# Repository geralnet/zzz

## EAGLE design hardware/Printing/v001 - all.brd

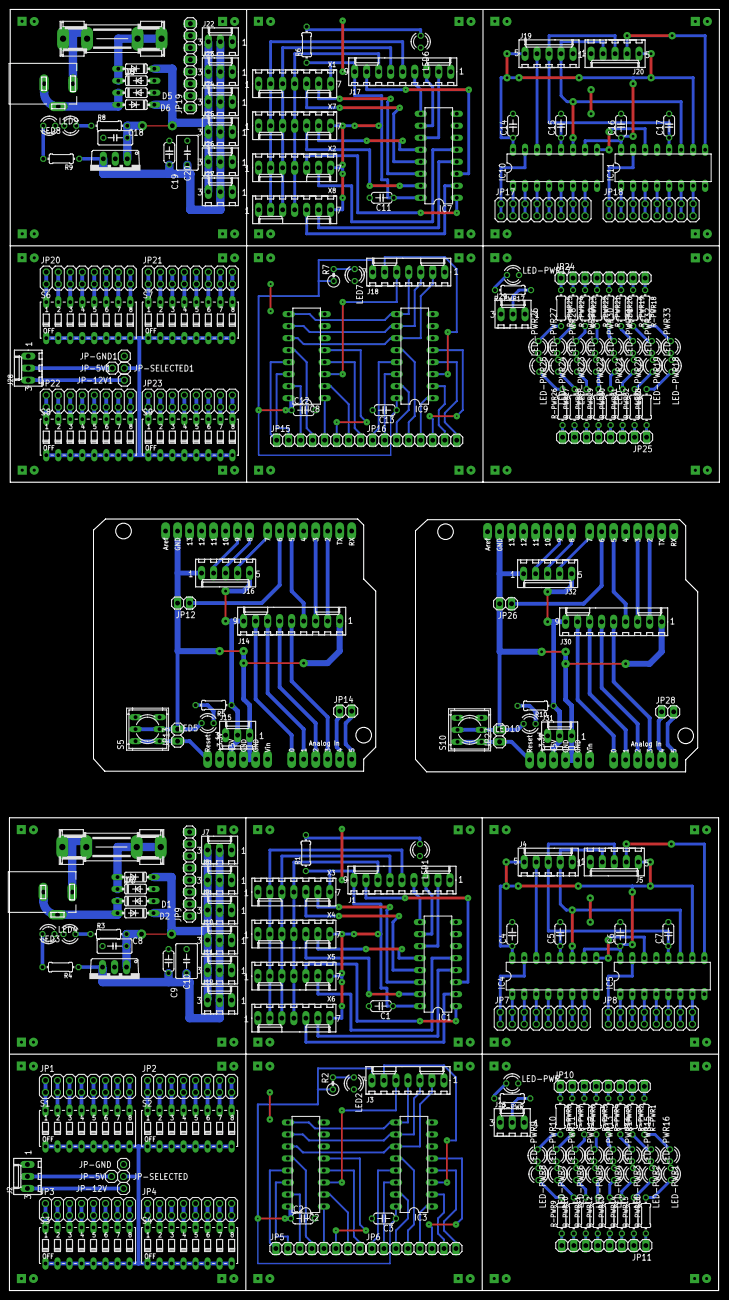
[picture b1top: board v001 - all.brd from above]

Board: 2 copper layers, 150.2 x 271.0 mm, 230 parts (0 on the bottom side), 322 nets.

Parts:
C1, C2, C3, C4, C5, C6, C7, C9, C11, C12, C13, C14, C15, C16, C17, C19: 0.1uF; C050-024X044
C8, C18: 0.33uF; C050-030X075
C10, C20: 1uF; C050-045X075
D1, D2, D3, D4, D5, D6, D7, D8: 1N4004; DO35-7
F1, F2: 3A; SHK20L
IC1, IC2, IC3, IC7, IC8, IC9: 4051N; DIL16
IC4, IC5, IC10, IC11: 74HC595N; DIL16
IC6, IC12: 7805TV; TO220V
J1, J17: To Arduino Shield; 6410-09
J2, J13, J15, J28, J29, J31: Power; 6410-03
J3, J18: Input; 6410-07
J4, J19: Input; 6410-05
J5, J20: Next Demux; 6410-05
J6, J21: 12VDC; DCJ0202
J7, J22: Out-1; 6410-03
J8, J23: Out-2; 6410-03
J9, J24: Out-3; 6410-03
J10, J25: Out-4; 6410-03
J11, J26: Out-5; 6410-03
J12, J27: Out-6; 6410-03
J14, J30: Primary Input Mux; 6410-09
J16, J32: Output Demux; 6410-05
JP1, JP2, JP3, JP4, JP20, JP21, JP22, JP23: 2X08
JP5, JP15: Input 1; 1X08
JP6, JP16: Input 2; 1X08
JP7, JP17: Output A; 2X08
JP8, JP18: Output B; 2X08
JP9, JP19: GND; 1X08
JP10, JP11, JP24, JP25: 1X08
JP12, JP14, JP26, JP28: Config; 1X02
JP13, JP27: Reset; 1X02
JP-5V, JP-5V1, JP-12V, JP-12V1: 1X01
JP-GND, JP-GND1: 1X01
JP-SELECTED, JP-SELECTED1: 1X01
LED1, LED2, LED5, LED6, LED7, LED10: Green; LED3MM
LED3, LED4, LED8, LED9: GREEN; LED3MM
LED-PWR, LED-PWR17: Green; LED3MM
LED-PWR1, LED-PWR2, LED-PWR3, LED-PWR4, LED-PWR5, LED-PWR6, LED-PWR7, LED-PWR8, LED-PWR9, LED-PWR10, LED-PWR11, LED-PWR12, LED-PWR13, LED-PWR14, LED-PWR15, LED-PWR16, LED-PWR18, LED-PWR19, LED-PWR20, LED-PWR21, LED-PWR22, LED-PWR23, LED-PWR24, LED-PWR25, LED-PWR26, LED-PWR27, LED-PWR28, LED-PWR29, LED-PWR30, LED-PWR31, LED-PWR32, LED-PWR33: Yellow; LED3MM
PCB1, PCB2, PCB3, PCB4, PCB5, PCB6, PCB7, PCB8, PCB9, PCB10, PCB11, PCB12: ZZZ_MODULE05X05; ZZZ_MODULE_05X05
R1, R3, R4, R5, R6, R8, R9, R10: 470R; 0204/7
R2, R7: 470R; 0207/2V
R-PWR, R-PWR1, R-PWR2, R-PWR3, R-PWR4, R-PWR5, R-PWR6, R-PWR7, R-PWR8, R-PWR9, R-PWR10, R-PWR11, R-PWR12, R-PWR13, R-PWR14, R-PWR15, R-PWR16, R-PWR17, R-PWR18, R-PWR19, R-PWR20, R-PWR21, R-PWR22, R-PWR23, R-PWR24, R-PWR25, R-PWR26, R-PWR27, R-PWR28, R-PWR29, R-PWR30, R-PWR31, R-PWR32, R-PWR33: 470R; 0204/7
S1, S2, S3, S4, S6, S7, S8, S9: DIP08S
S5, S10: 9077-2
U1, U2: ARDUINO_SHIELDLONGPADS; DUEMILANOVE_SHIELD_LONGPADS
X1, X3: Sec 12; 6410-07
X2, X5: Sec 56; 6410-07
X4, X7: Sec 34; 6410-07
X6, X8: Sec 78; 6410-07

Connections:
!CONFIGURATION: JP12.1, U1.D6
!CONFIGURATION1: JP26.1, U2.D6
!RESET: JP13.1, S5.1, S5.4, U1.RES
!RESET1: JP27.1, S10.1, S10.4, U2.RES
+5V: J2.2, JP-5V.1
+5V1: C1.1, IC1.16, J1.9, R1.1, X3.7, X4.7, X5.7, X6.7
+5V2: C2.1, C3.1, IC2.16, IC3.16, J3.7, R2.1
+5V3: C4.1, C6.1, IC4.10, IC4.16, IC5.10, IC5.16, J4.5, J5.5
+5V4: C9.1, C10.1, IC6.3, J7.2, J8.2, J9.2, J10.2, J11.2, J12.2, R4.1
+5V5: J13.2, R-PWR.1
+5V6: J14.9, J15.2, J16.5, R5.1, U1.5V
+5V7: C11.1, IC7.16, J17.9, R6.1, X1.7, X2.7, X7.7, X8.7
+5V8: C12.1, C13.1, IC8.16, IC9.16, J18.7, R7.1
+5V9: C14.1, C16.1, IC10.10, IC10.16, IC11.10, IC11.16, J19.5, J20.5
+5V10: C19.1, C20.1, IC12.3, J22.2, J23.2, J24.2, J25.2, J26.2, J27.2, R9.1
+5V11: J28.2, JP-5V1.1
+5V12: J29.2, R-PWR17.1
+5V13: J30.9, J31.2, J32.5, R10.1, U2.5V
+12V: J2.3, JP-12V.1
+12V1: C8.1, D2.C, D4.C, IC6.1, J7.3, J8.3, J9.3, J10.3, J11.3, J12.3, R3.2
+12V3: C18.1, D6.C, D8.C, IC12.1, J22.3, J23.3, J24.3, J25.3, J26.3, J27.3, R8.2
+12V4: J28.3, JP-12V1.1
GND: J2.1, JP-GND.1, PCB1.GND@1, PCB1.GND@2, PCB1.GND@3, PCB1.GND@4, PCB1.GND@5, PCB1.GND@6, PCB1.GND@7, PCB1.GND@8
GND1: C1.2, IC1.6, IC1.7, IC1.8, J1.1, LED1.K, PCB2.GND@1, PCB2.GND@2, PCB2.GND@3, PCB2.GND@4, PCB2.GND@5, PCB2.GND@6, PCB2.GND@7, PCB2.GND@8, X3.1, X4.1, X5.1, X6.1
GND2: C2.2, C3.2, IC2.6, IC2.7, IC2.8, IC3.6, IC3.7, IC3.8, J3.1, LED2.K, PCB3.GND@1, PCB3.GND@2, PCB3.GND@3, PCB3.GND@4, PCB3.GND@5, PCB3.GND@6, PCB3.GND@7, PCB3.GND@8
GND3: C4.2, C5.2, C6.2, C7.2, IC4.8, IC4.13, IC5.8, IC5.13, J4.1, J5.1, PCB4.GND@1, PCB4.GND@2, PCB4.GND@3, PCB4.GND@4, PCB4.GND@5, PCB4.GND@6, PCB4.GND@7, PCB4.GND@8
GND4: C8.2, C9.2, C10.2, D1.A, D3.A, IC6.2, J7.1, J8.1, J9.1, J10.1, J11.1, J12.1, JP9.1, JP9.2, JP9.3, JP9.4, JP9.5, JP9.6, JP9.7, JP9.8, LED3.K, LED4.K, PCB5.GND@1, PCB5.GND@2, PCB5.GND@3, PCB5.GND@4, PCB5.GND@5, PCB5.GND@6, PCB5.GND@7, PCB5.GND@8
GND5: J13.1, LED-PWR.K, LED-PWR1.K, LED-PWR2.K, LED-PWR3.K, LED-PWR4.K, LED-PWR5.K, LED-PWR6.K, LED-PWR7.K, LED-PWR8.K, LED-PWR9.K, LED-PWR10.K, LED-PWR11.K, LED-PWR12.K, LED-PWR13.K, LED-PWR14.K, LED-PWR15.K, LED-PWR16.K, PCB6.GND@1, PCB6.GND@2, PCB6.GND@3, PCB6.GND@4, PCB6.GND@5, PCB6.GND@6, PCB6.GND@7, PCB6.GND@8
GND6: J14.1, J15.1, J16.1, JP12.2, JP13.2, LED5.K, S5.2, S5.5, U1.GND@0, U1.GND@1, U1.GND@2
GND7: C11.2, IC7.6, IC7.7, IC7.8, J17.1, LED6.K, PCB7.GND@1, PCB7.GND@2, PCB7.GND@3, PCB7.GND@4, PCB7.GND@5, PCB7.GND@6, PCB7.GND@7, PCB7.GND@8, X1.1, X2.1, X7.1, X8.1
GND8: C12.2, C13.2, IC8.6, IC8.7, IC8.8, IC9.6, IC9.7, IC9.8, J18.1, LED7.K, PCB8.GND@1, PCB8.GND@2, PCB8.GND@3, PCB8.GND@4, PCB8.GND@5, PCB8.GND@6, PCB8.GND@7, PCB8.GND@8
GND9: C14.2, C15.2, C16.2, C17.2, IC10.8, IC10.13, IC11.8, IC11.13, J19.1, J20.1, PCB9.GND@1, PCB9.GND@2, PCB9.GND@3, PCB9.GND@4, PCB9.GND@5, PCB9.GND@6, PCB9.GND@7, PCB9.GND@8
GND10: C18.2, C19.2, C20.2, D5.A, D7.A, IC12.2, J22.1, J23.1, J24.1, J25.1, J26.1, J27.1, JP19.1, JP19.2, JP19.3, JP19.4, JP19.5, JP19.6, JP19.7, JP19.8, LED8.K, LED9.K, PCB10.GND@1, PCB10.GND@2, PCB10.GND@3, PCB10.GND@4, PCB10.GND@5, PCB10.GND@6, PCB10.GND@7, PCB10.GND@8
GND11: J28.1, JP-GND1.1, PCB11.GND@1, PCB11.GND@2, PCB11.GND@3, PCB11.GND@4, PCB11.GND@5, PCB11.GND@6, PCB11.GND@7, PCB11.GND@8
GND12: J29.1, LED-PWR17.K, LED-PWR18.K, LED-PWR19.K, LED-PWR20.K, LED-PWR21.K, LED-PWR22.K, LED-PWR23.K, LED-PWR24.K, LED-PWR25.K, LED-PWR26.K, LED-PWR27.K, LED-PWR28.K, LED-PWR29.K, LED-PWR30.K, LED-PWR31.K, LED-PWR32.K, LED-PWR33.K, PCB12.GND@1, PCB12.GND@2, PCB12.GND@3, PCB12.GND@4, PCB12.GND@5, PCB12.GND@6, PCB12.GND@7, PCB12.GND@8
GND13: J30.1, J31.1, J32.1, JP26.2, JP27.2, LED10.K, S10.2, S10.5, U2.GND@0, U2.GND@1, U2.GND@2
INPUT_1: IC2.13, JP5.1
INPUT_2: IC2.14, JP5.2
INPUT_3: IC2.15, JP5.3
INPUT_4: IC2.12, JP5.4
INPUT_5: IC2.1, JP5.5
INPUT_6: IC2.5, JP5.6
INPUT_7: IC2.2, JP5.7
INPUT_8: IC2.4, JP5.8
INPUT_9: IC3.13, JP6.1
INPUT_10: IC3.14, JP6.2
INPUT_11: IC3.15, JP6.3
INPUT_12: IC3.12, JP6.4
INPUT_13: IC3.1, JP6.5
INPUT_14: IC3.5, JP6.6
INPUT_15: IC3.2, JP6.7
INPUT_16: IC8.13, JP15.1
INPUT_17: IC8.14, JP15.2
INPUT_18: IC8.15, JP15.3
INPUT_19: IC8.12, JP15.4
INPUT_20: IC8.1, JP15.5
INPUT_21: IC8.5, JP15.6
INPUT_22: IC8.2, JP15.7
INPUT_23: IC8.4, JP15.8
INPUT_24: IC9.13, JP16.1
INPUT_25: IC9.14, JP16.2
INPUT_26: IC9.15, JP16.3
INPUT_27: IC9.12, JP16.4
INPUT_28: IC9.1, JP16.5
INPUT_29: IC9.5, JP16.6
INPUT_30: IC9.2, JP16.7
INPUT_READ: IC1.3, J1.8
INPUT_READ1: J14.8, U1.A0
INPUT_READ2: IC7.3, J17.8
INPUT_READ3: J30.8, U2.A0
IN_CLOCK: IC4.11, IC5.11, J4.2, J5.2
IN_CLOCK1: IC10.11, IC11.11, J19.2, J20.2
IN_DATA: IC4.14, J4.4
IN_DATA1: IC10.14, J19.4
IN_LATCH: C5.1, C7.1, IC4.12, IC5.12, J4.3, J5.3
IN_LATCH1: C15.1, C17.1, IC10.12, IC11.12, J19.3, J20.3
IN_SELECT_A: J14.2, U1.D2
IN_SELECT_A1: J30.2, U2.D2
IN_SELECT_B: J14.3, U1.D3
IN_SELECT_B1: J30.3, U2.D3
IN_SELECT_C: J14.4, U1.D5
IN_SELECT_C1: J30.4, U2.D5
IN_SELECT_D: J14.5, U1.A3
IN_SELECT_D1: J30.5, U2.A3
IN_SELECT_E: J14.6, U1.A2
IN_SELECT_E1: J30.6, U2.A2
IN_SELECT_F: J14.7, U1.A1
IN_SELECT_F1: J30.7, U2.A1
unnamed: JP3.1, JP3.2, S3.16
unnamed: JP3.3, JP3.4, S3.15
unnamed: LED1.A, R1.2
unnamed: JP1.1, JP1.2, S1.16
unnamed: JP1.3, JP1.4, S1.15
unnamed: JP1.5, JP1.6, S1.14
unnamed: JP1.7, JP1.8, S1.13
unnamed: JP1.9, JP1.10, S1.12
unnamed: JP1.11, JP1.12, S1.11
unnamed: JP1.13, JP1.14, S1.10
unnamed: JP1.15, JP1.16, S1.9
unnamed: JP2.1, JP2.2, S2.16
unnamed: JP2.3, JP2.4, S2.15
unnamed: JP2.5, JP2.6, S2.14
unnamed: JP2.7, JP2.8, S2.13
unnamed: JP2.9, JP2.10, S2.12
unnamed: JP2.11, JP2.12, S2.11
unnamed: JP2.13, JP2.14, S2.10
unnamed: JP2.15, JP2.16, S2.9
unnamed: JP3.5, JP3.6, S3.14
unnamed: JP3.7, JP3.8, S3.13
unnamed: JP3.9, JP3.10, S3.12
unnamed: JP3.11, JP3.12, S3.11
unnamed: JP3.13, JP3.14, S3.10
unnamed: JP3.15, JP3.16, S3.9
unnamed: JP4.1, JP4.2, S4.16
unnamed: JP4.3, JP4.4, S4.15
unnamed: JP4.5, JP4.6, S4.14
unnamed: JP4.7, JP4.8, S4.13
unnamed: JP4.9, JP4.10, S4.12
unnamed: JP4.11, JP4.12, S4.11
unnamed: JP4.13, JP4.14, S4.10
unnamed: JP4.15, JP4.16, S4.9
unnamed: JP-SELECTED.1, S1.1, S1.2, S1.3, S1.4, S1.5, S1.6, S1.7, S1.8, S2.1, S2.2, S2.3, S2.4, S2.5, S2.6, S2.7, S2.8, S3.1, S3.2, S3.3, S3.4, S3.5, S3.6, S3.7, S3.8, S4.1, S4.2, S4.3, S4.4, S4.5, S4.6, S4.7, S4.8
unnamed: LED2.A, R2.2
unnamed: IC3.4, JP6.8
unnamed: IC4.15, JP7.1, JP7.2
unnamed: IC4.1, JP7.3, JP7.4
unnamed: IC4.2, JP7.5, JP7.6
unnamed: IC4.3, JP7.7, JP7.8
unnamed: IC4.4, JP7.9, JP7.10
unnamed: IC4.5, JP7.11, JP7.12
unnamed: IC4.6, JP7.13, JP7.14
unnamed: IC4.7, JP7.15, JP7.16
unnamed: IC5.15, JP8.1, JP8.2
unnamed: IC5.1, JP8.3, JP8.4
unnamed: IC5.2, JP8.5, JP8.6
unnamed: IC5.3, JP8.7, JP8.8
unnamed: IC5.4, JP8.9, JP8.10
unnamed: IC5.5, JP8.11, JP8.12
unnamed: IC5.6, JP8.13, JP8.14
unnamed: IC5.7, JP8.15, JP8.16
unnamed: IC4.9, IC5.14
unnamed: D1.C, D2.A, J6.2, J6.3
unnamed: D3.C, D4.A, F1.2A
unnamed: LED3.A, R3.1
unnamed: LED4.A, R4.2
unnamed: F1.1A, J6.1
unnamed: LED-PWR.A, R-PWR.2
unnamed: JP10.8, R-PWR1.1
unnamed: JP10.7, R-PWR2.1
unnamed: JP10.6, R-PWR3.1
unnamed: JP10.5, R-PWR4.1
unnamed: JP10.4, R-PWR5.1
unnamed: JP10.3, R-PWR6.1
unnamed: JP10.2, R-PWR7.1
unnamed: JP10.1, R-PWR8.1
unnamed: LED-PWR1.A, R-PWR1.2
unnamed: LED-PWR2.A, R-PWR2.2
unnamed: LED-PWR3.A, R-PWR3.2
unnamed: LED-PWR4.A, R-PWR4.2
unnamed: LED-PWR5.A, R-PWR5.2
unnamed: LED-PWR6.A, R-PWR6.2
unnamed: LED-PWR7.A, R-PWR7.2
unnamed: LED-PWR8.A, R-PWR8.2
unnamed: JP11.8, R-PWR9.1
unnamed: JP11.7, R-PWR10.1
unnamed: JP11.6, R-PWR11.1
unnamed: JP11.5, R-PWR12.1
unnamed: JP11.4, R-PWR13.1
unnamed: JP11.3, R-PWR14.1
unnamed: JP11.2, R-PWR15.1
unnamed: JP11.1, R-PWR16.1
unnamed: LED-PWR9.A, R-PWR9.2
unnamed: LED-PWR10.A, R-PWR10.2
unnamed: LED-PWR11.A, R-PWR11.2
unnamed: LED-PWR12.A, R-PWR12.2
unnamed: LED-PWR13.A, R-PWR13.2
unnamed: LED-PWR14.A, R-PWR14.2
unnamed: LED-PWR15.A, R-PWR15.2
unnamed: LED-PWR16.A, R-PWR16.2
unnamed: LED5.A, R5.2
unnamed: LED6.A, R6.2
unnamed: LED7.A, R7.2
unnamed: IC9.4, JP16.8
unnamed: IC10.15, JP17.1, JP17.2
unnamed: IC10.1, JP17.3, JP17.4
unnamed: IC10.2, JP17.5, JP17.6
unnamed: IC10.3, JP17.7, JP17.8
unnamed: IC10.4, JP17.9, JP17.10
unnamed: IC10.5, JP17.11, JP17.12
unnamed: IC10.6, JP17.13, JP17.14
unnamed: IC10.7, JP17.15, JP17.16
unnamed: IC11.15, JP18.1, JP18.2
unnamed: IC11.1, JP18.3, JP18.4
unnamed: IC11.2, JP18.5, JP18.6
unnamed: IC11.3, JP18.7, JP18.8
unnamed: IC11.4, JP18.9, JP18.10
unnamed: IC11.5, JP18.11, JP18.12
unnamed: IC11.6, JP18.13, JP18.14
unnamed: IC11.7, JP18.15, JP18.16
unnamed: IC10.9, IC11.14
unnamed: D5.C, D6.A, J21.2, J21.3
unnamed: D7.C, D8.A, F2.2A
unnamed: LED8.A, R8.1
unnamed: LED9.A, R9.2
unnamed: F2.1A, J21.1
unnamed: JP20.1, JP20.2, S6.16
unnamed: JP20.3, JP20.4, S6.15
unnamed: JP20.5, JP20.6, S6.14
unnamed: JP20.7, JP20.8, S6.13
unnamed: JP20.9, JP20.10, S6.12
unnamed: JP20.11, JP20.12, S6.11
unnamed: JP20.13, JP20.14, S6.10
unnamed: JP20.15, JP20.16, S6.9
unnamed: JP21.1, JP21.2, S7.16
unnamed: JP21.3, JP21.4, S7.15
unnamed: JP21.5, JP21.6, S7.14
unnamed: JP21.7, JP21.8, S7.13
unnamed: JP21.9, JP21.10, S7.12
unnamed: JP21.11, JP21.12, S7.11
unnamed: JP21.13, JP21.14, S7.10
unnamed: JP21.15, JP21.16, S7.9
unnamed: JP22.1, JP22.2, S8.16
unnamed: JP22.3, JP22.4, S8.15
unnamed: JP22.5, JP22.6, S8.14
unnamed: JP22.7, JP22.8, S8.13
unnamed: JP22.9, JP22.10, S8.12
unnamed: JP22.11, JP22.12, S8.11
unnamed: JP22.13, JP22.14, S8.10
unnamed: JP22.15, JP22.16, S8.9
unnamed: JP23.1, JP23.2, S9.16
unnamed: JP23.3, JP23.4, S9.15
unnamed: JP23.5, JP23.6, S9.14
unnamed: JP23.7, JP23.8, S9.13
unnamed: JP23.9, JP23.10, S9.12
unnamed: JP23.11, JP23.12, S9.11
unnamed: JP23.13, JP23.14, S9.10
unnamed: JP23.15, JP23.16, S9.9
unnamed: JP-SELECTED1.1, S6.1, S6.2, S6.3, S6.4, S6.5, S6.6, S6.7, S6.8, S7.1, S7.2, S7.3, S7.4, S7.5, S7.6, S7.7, S7.8, S8.1, S8.2, S8.3, S8.4, S8.5, S8.6, S8.7, S8.8, S9.1, S9.2, S9.3, S9.4, S9.5, S9.6, S9.7, S9.8
unnamed: LED-PWR17.A, R-PWR17.2
unnamed: JP24.8, R-PWR18.1
unnamed: JP24.7, R-PWR19.1
unnamed: JP24.6, R-PWR20.1
unnamed: JP24.5, R-PWR21.1
unnamed: JP24.4, R-PWR22.1
unnamed: JP24.3, R-PWR23.1
unnamed: JP24.2, R-PWR24.1
unnamed: JP24.1, R-PWR25.1
unnamed: LED-PWR18.A, R-PWR18.2
unnamed: LED-PWR19.A, R-PWR19.2
unnamed: LED-PWR20.A, R-PWR20.2
unnamed: LED-PWR21.A, R-PWR21.2
unnamed: LED-PWR22.A, R-PWR22.2
unnamed: LED-PWR23.A, R-PWR23.2
unnamed: LED-PWR24.A, R-PWR24.2
unnamed: LED-PWR25.A, R-PWR25.2
unnamed: JP25.8, R-PWR26.1
unnamed: JP25.7, R-PWR27.1
unnamed: JP25.6, R-PWR28.1
unnamed: JP25.5, R-PWR29.1
unnamed: JP25.4, R-PWR30.1
unnamed: JP25.3, R-PWR31.1
unnamed: JP25.2, R-PWR32.1
unnamed: JP25.1, R-PWR33.1
unnamed: LED-PWR26.A, R-PWR26.2
unnamed: LED-PWR27.A, R-PWR27.2
unnamed: LED-PWR28.A, R-PWR28.2
unnamed: LED-PWR29.A, R-PWR29.2
unnamed: LED-PWR30.A, R-PWR30.2
unnamed: LED-PWR31.A, R-PWR31.2
unnamed: LED-PWR32.A, R-PWR32.2
unnamed: LED-PWR33.A, R-PWR33.2
unnamed: LED10.A, R10.2
NEXT_DEMUX: IC5.9, J5.4
NEXT_DEMUX1: IC11.9, J20.4
OUT_CLOCK_ETHLED: J16.2, U1.D9
OUT_CLOCK_ETHLED1: J32.2, U2.D9
OUT_DATA: J16.4, U1.D7
OUT_DATA1: J32.4, U2.D7
OUT_LATCH: J16.3, U1.D8
OUT_LATCH1: J32.3, U2.D8
RESERVED_1: JP14.1, U1.A4
RESERVED_2: JP14.2, U1.A5
RESERVED_3: JP28.1, U2.A4
RESERVED_4: JP28.2, U2.A5
SECONDARY_1: IC1.13, X3.5
SECONDARY_2: IC1.14, X3.6
SECONDARY_3: IC1.15, X4.5
SECONDARY_4: IC1.12, X4.6
SECONDARY_5: IC1.1, X5.5
SECONDARY_6: IC1.5, X5.6
SECONDARY_7: IC1.2, X6.5
SECONDARY_8: IC1.4, X6.6
SECONDARY_9: IC2.3, J3.5
SECONDARY_10: IC3.3, J3.6
SECONDARY_11: IC7.13, X1.5
SECONDARY_12: IC7.14, X1.6
SECONDARY_13: IC7.15, X7.5
SECONDARY_14: IC7.12, X7.6
SECONDARY_15: IC7.1, X2.5
SECONDARY_16: IC7.5, X2.6
SECONDARY_17: IC7.2, X8.5
SECONDARY_18: IC7.4, X8.6
SECONDARY_19: IC8.3, J18.5
SECONDARY_20: IC9.3, J18.6
SELECT_A: IC1.11, J1.2
SELECT_A1: IC7.11, J17.2
SELECT_B: IC1.10, J1.3
SELECT_B1: IC7.10, J17.3
SELECT_C: IC1.9, J1.4
SELECT_C1: IC7.9, J17.4
SELECT_D: J1.5, X3.2, X4.2, X5.2, X6.2
SELECT_D1: IC2.11, IC3.11, J3.2
SELECT_D2: J17.5, X1.2, X2.2, X7.2, X8.2
SELECT_D3: IC8.11, IC9.11, J18.2
SELECT_E: J1.6, X3.3, X4.3, X5.3, X6.3
SELECT_E1: IC2.10, IC3.10, J3.3
SELECT_E2: J17.6, X1.3, X2.3, X7.3, X8.3
SELECT_E3: IC8.10, IC9.10, J18.3
SELECT_F: J1.7, X3.4, X4.4, X5.4, X6.4
SELECT_F1: IC2.9, IC3.9, J3.4
SELECT_F2: J17.7, X1.4, X2.4, X7.4, X8.4
SELECT_F3: IC8.9, IC9.9, J18.4

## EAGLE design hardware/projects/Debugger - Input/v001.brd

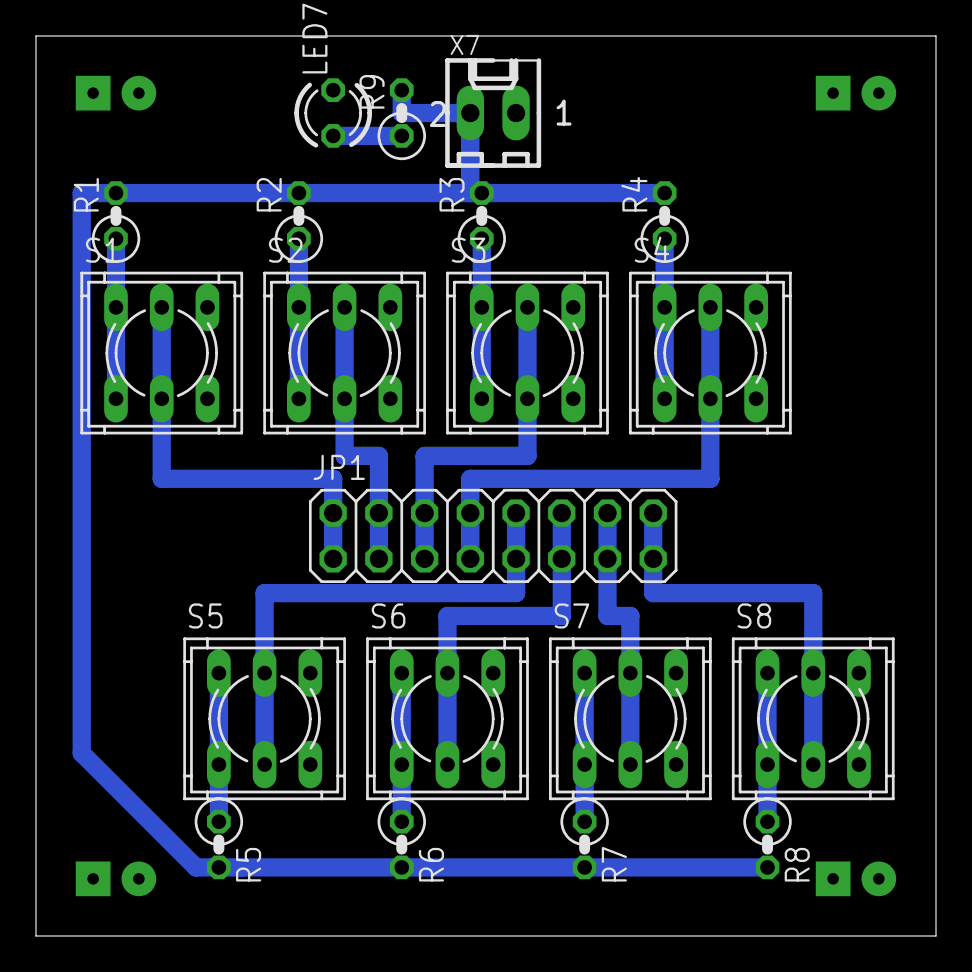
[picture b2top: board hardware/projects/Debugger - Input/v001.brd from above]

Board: 2 copper layers, 50.0 x 50.0 mm, 21 parts (0 on the bottom side), 19 nets.

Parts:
JP1: Output; 2X08
LED7: Green; LED3MM
PCB1: PCB05X05; PCB_05X05
R1, R2, R3, R4, R5, R6, R7, R8: 1K; 0207/2V
R9: 470R; 0207/2V
S1, S2, S3, S4, S5, S6, S7, S8: 9077-2
X7: Power; 6410-02

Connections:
+5V: R1.2, R2.2, R3.2, R4.2, R5.2, R6.2, R7.2, R8.2, R9.2, X7.2
GND: LED7.K, PCB1.GND@1, PCB1.GND@2, PCB1.GND@3, PCB1.GND@4, PCB1.GND@5, PCB1.GND@6, PCB1.GND@7, PCB1.GND@8, S1.3, S1.6, S2.3, S2.6, S3.3, S3.6, S4.3, S4.6, S5.3, S5.6, S6.3, S6.6, S7.3, S7.6, S8.3, S8.6, X7.1
unnamed: R4.1, S4.1, S4.4
unnamed: R3.1, S3.1, S3.4
unnamed: R2.1, S2.1, S2.4
unnamed: R1.1, S1.1, S1.4
unnamed: R8.1, S8.1, S8.4
unnamed: R7.1, S7.1, S7.4
unnamed: R6.1, S6.1, S6.4
unnamed: R5.1, S5.1, S5.4
unnamed: LED7.A, R9.1
OUT1: JP1.1, JP1.2, S1.2, S1.5
OUT2: JP1.3, JP1.4, S2.2, S2.5
OUT3: JP1.5, JP1.6, S3.2, S3.5
OUT4: JP1.7, JP1.8, S4.2, S4.5
OUT5: JP1.9, JP1.10, S5.2, S5.5
OUT6: JP1.11, JP1.12, S6.2, S6.5
OUT7: JP1.13, JP1.14, S7.2, S7.5
OUT8: JP1.15, JP1.16, S8.2, S8.5

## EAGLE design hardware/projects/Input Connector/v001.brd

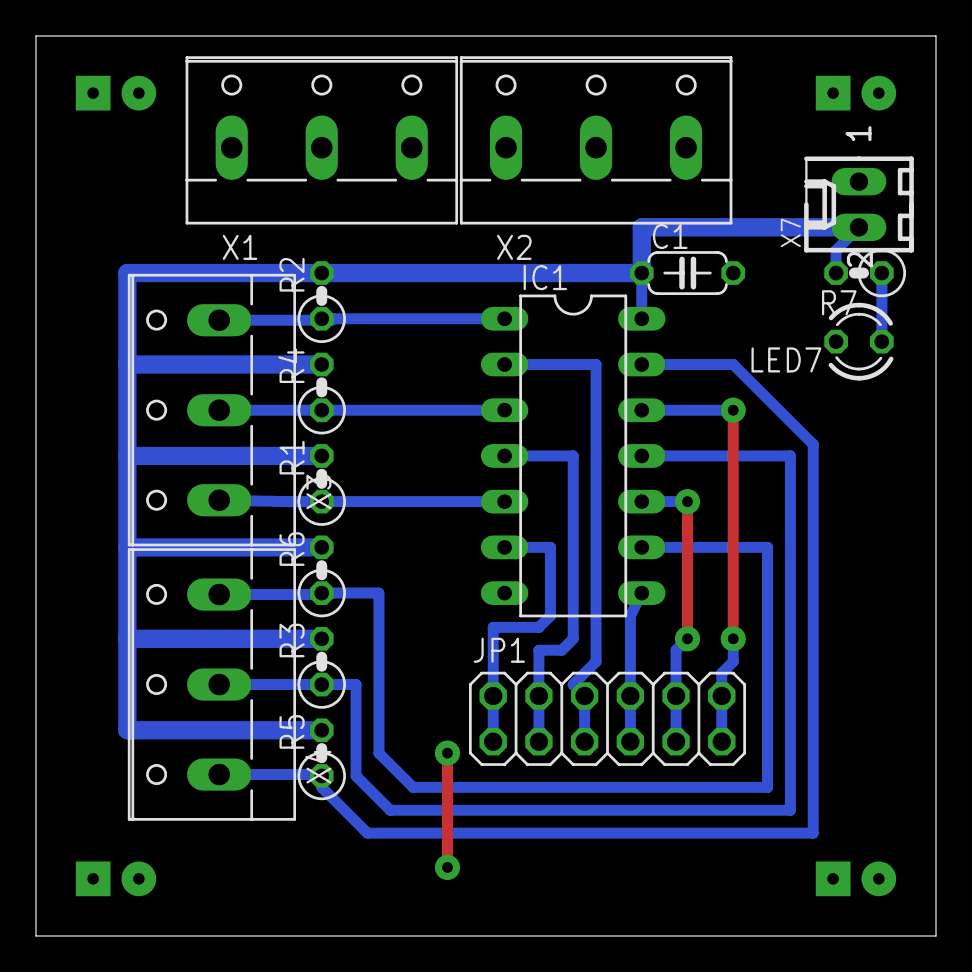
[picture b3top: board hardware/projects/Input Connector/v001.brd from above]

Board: 2 copper layers, 50.0 x 50.0 mm, 17 parts (0 on the bottom side), 15 nets.

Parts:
C1: 0.1uF; C050-024X044
IC1: 7404; DIL14
JP1: Output; 2X06
LED7: Green; LED3MM
PCB1: PCB05X05; PCB_05X05
R1, R2, R3, R4, R5, R6: 10K; 0207/2V
R7: 470R; 0207/2V
X1, X2: GND; W237-103
X3, X4: W237-103
X7: Power; 6410-02

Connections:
+5V: C1.1, IC1.14, R1.2, R2.2, R3.2, R4.2, R5.2, R6.2, R7.2, X7.2
GND: C1.2, IC1.7, LED7.K, PCB1.GND@1, PCB1.GND@2, PCB1.GND@3, PCB1.GND@4, PCB1.GND@5, PCB1.GND@6, PCB1.GND@7, PCB1.GND@8, X1.1, X1.2, X1.3, X2.1, X2.2, X2.3, X7.1
unnamed: IC1.2, JP1.5, JP1.6
unnamed: IC1.1, R2.1, X3.3
unnamed: IC1.6, JP1.1, JP1.2
unnamed: IC1.5, R1.1, X3.1
unnamed: IC1.11, R3.1, X4.2
unnamed: IC1.10, JP1.9, JP1.10
unnamed: IC1.3, R4.1, X3.2
unnamed: IC1.12, JP1.11, JP1.12
unnamed: IC1.13, R5.1, X4.1
unnamed: IC1.8, JP1.7, JP1.8
unnamed: IC1.9, R6.1, X4.3
unnamed: IC1.4, JP1.3, JP1.4
unnamed: LED7.A, R7.1

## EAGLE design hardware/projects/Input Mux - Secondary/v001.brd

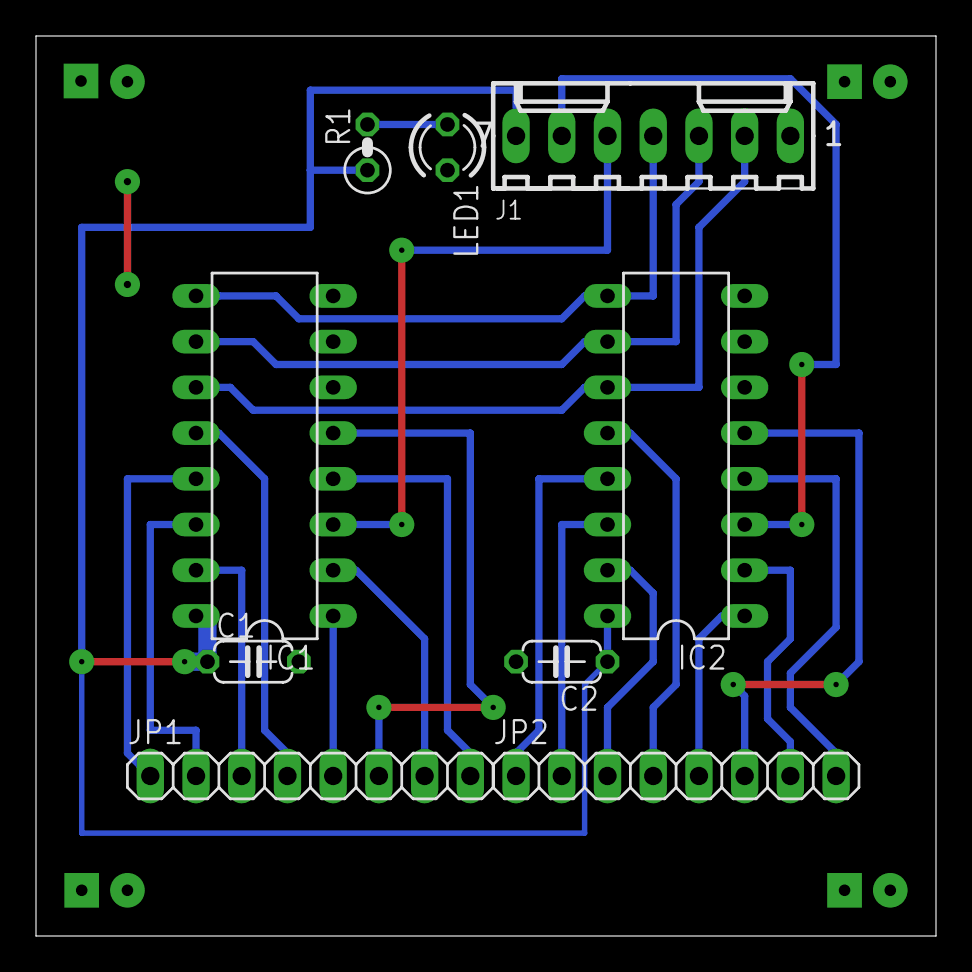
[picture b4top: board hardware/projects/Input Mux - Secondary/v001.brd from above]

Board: 2 copper layers, 50.0 x 50.0 mm, 10 parts (0 on the bottom side), 24 nets.

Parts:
C1, C2: 0.1uF; C050-024X044
IC1, IC2: 4051N; DIL16
J1: Input; 6410-07
JP1: Input 1; 1X08
JP2: Input 2; 1X08
LED1: Green; LED3MM
PCB1: ZZZ_MODULE05X05; ZZZ_MODULE_05X05
R1: 470R; 0207/2V

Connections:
+5V: C1.1, C2.1, IC1.16, IC2.16, J1.7, R1.1
GND: C1.2, C2.2, IC1.6, IC1.7, IC1.8, IC2.6, IC2.7, IC2.8, J1.1, LED1.K, PCB1.GND@1, PCB1.GND@2, PCB1.GND@3, PCB1.GND@4, PCB1.GND@5, PCB1.GND@6, PCB1.GND@7, PCB1.GND@8
INPUT_1: IC1.13, JP1.1
INPUT_2: IC1.14, JP1.2
INPUT_3: IC1.15, JP1.3
INPUT_4: IC1.12, JP1.4
INPUT_5: IC1.1, JP1.5
INPUT_6: IC1.5, JP1.6
INPUT_7: IC1.2, JP1.7
INPUT_8: IC1.4, JP1.8
INPUT_9: IC2.13, JP2.1
INPUT_10: IC2.14, JP2.2
INPUT_11: IC2.15, JP2.3
INPUT_12: IC2.12, JP2.4
INPUT_13: IC2.1, JP2.5
INPUT_14: IC2.5, JP2.6
INPUT_15: IC2.2, JP2.7
unnamed: LED1.A, R1.2
unnamed: IC2.4, JP2.8
SECONDARY_1: IC1.3, J1.5
SECONDARY_2: IC2.3, J1.6
SELECT_D: IC1.11, IC2.11, J1.2
SELECT_E: IC1.10, IC2.10, J1.3
SELECT_F: IC1.9, IC2.9, J1.4

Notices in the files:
parts and their libraries:
SparkFun-Boards: Licensing: CC v3.0 Share-Alike You are welcome to use this library for commercial purposes.
